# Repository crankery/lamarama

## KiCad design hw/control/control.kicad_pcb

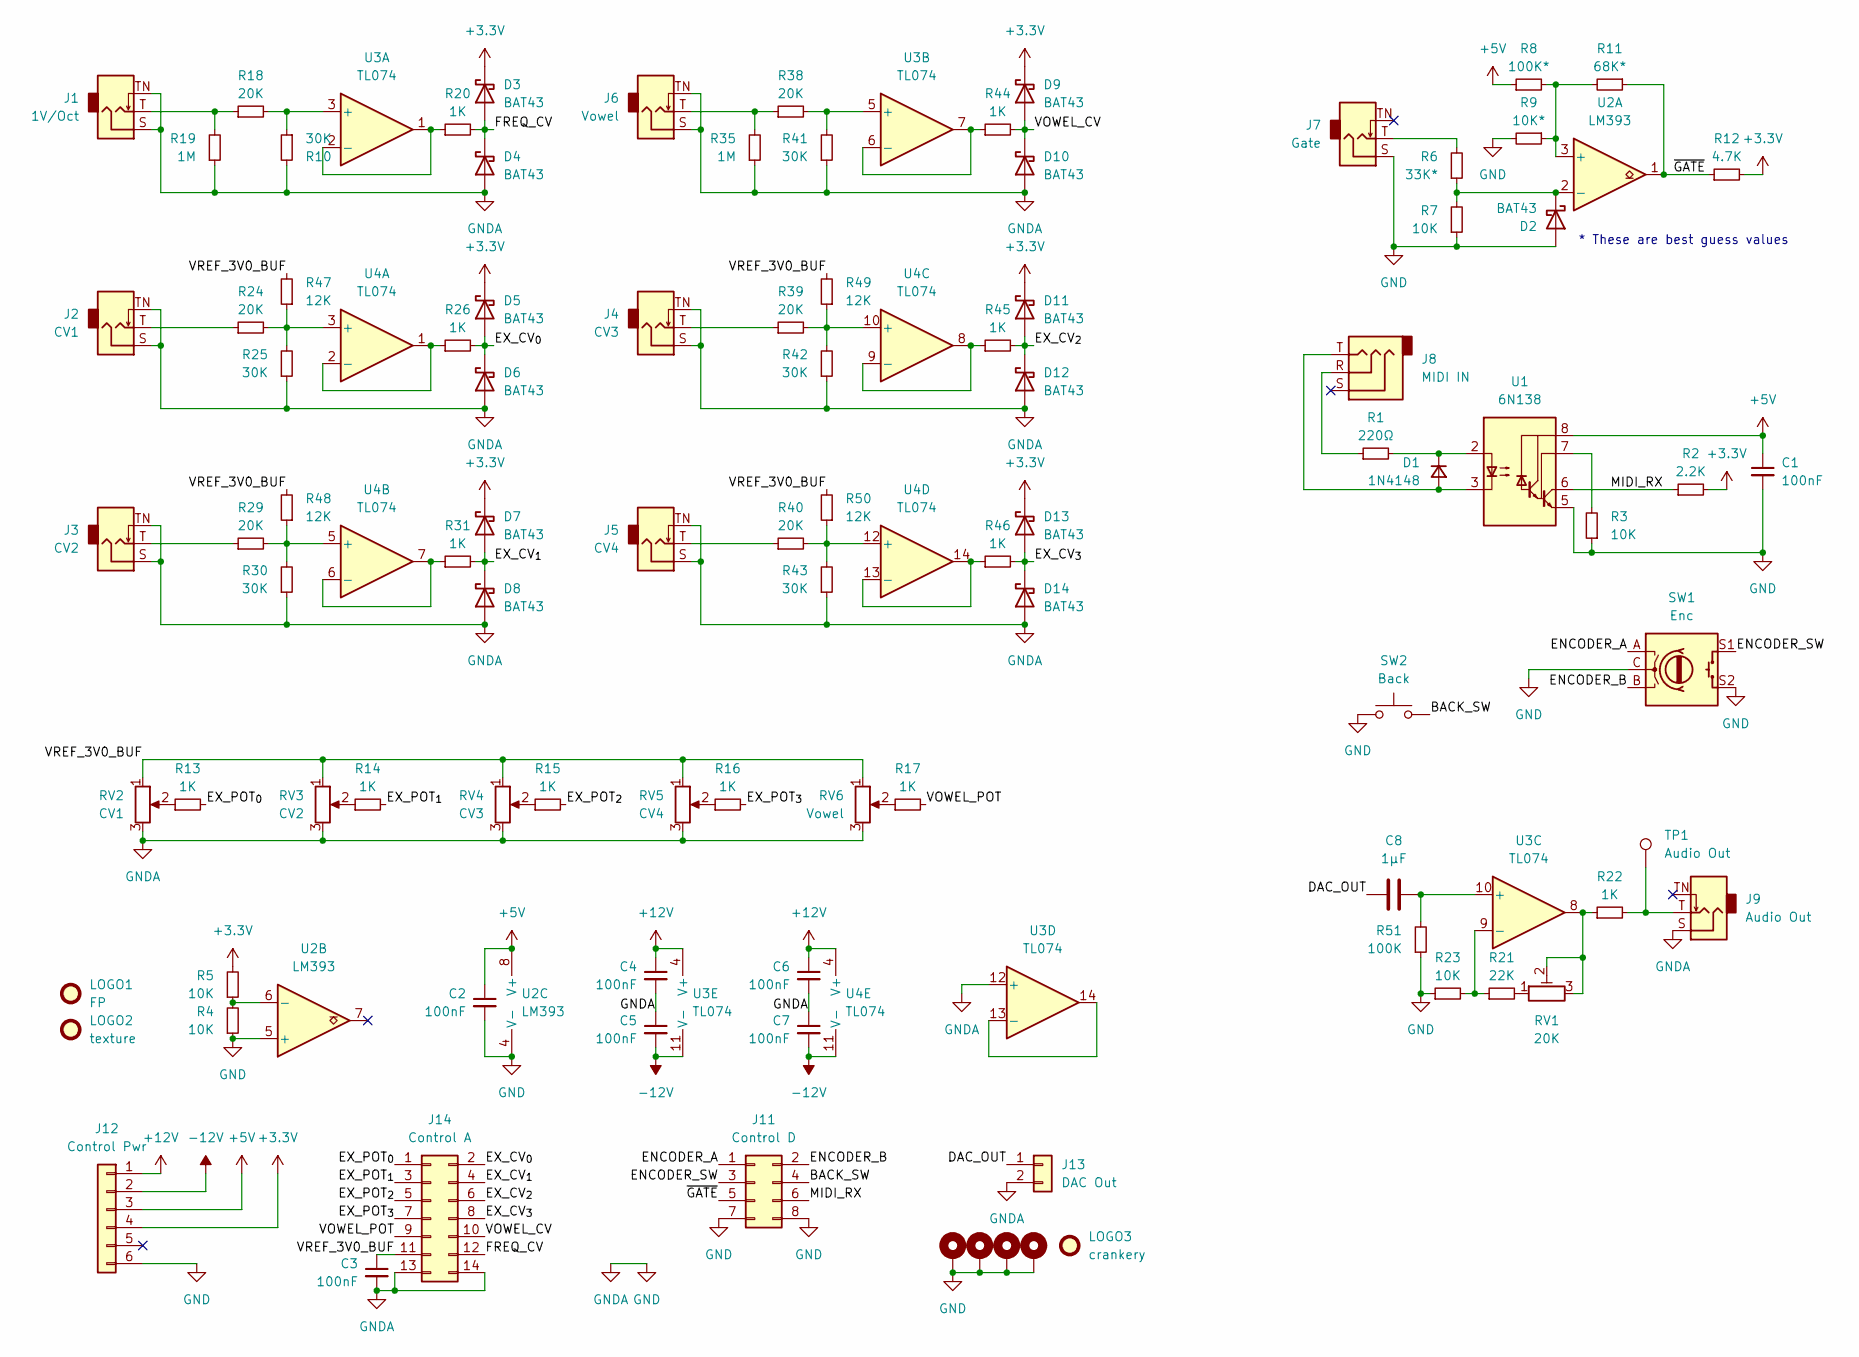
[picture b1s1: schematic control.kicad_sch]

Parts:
C1, C2, C3, C4, C5, C6, C7: 100nF; C_Disc_D3.0mm_W1.6mm_P2.50mm
C8: 1µF; C_Rect_L7.0mm_W2.5mm_P5.00mm
D1: 1N4148; D_DO-35_SOD27_P7.62mm_Horizontal
D2, D3, D4, D5, D6, D7, D8, D9, D10, D11, D12, D13, D14: BAT43; D_DO-35_SOD27_P7.62mm_Horizontal
H1, H2, H3, H4: MountingHole_Pad; MountingHole_3.2mm_M3_DIN965_Pad
J1: 1V/Oct; Jack_PJ398SM
J2: CV1; Jack_PJ398SM
J3: CV2; Jack_PJ398SM
J4: CV3; Jack_PJ398SM
J5: CV4; Jack_PJ398SM
J6: Vowel; Jack_PJ398SM
J7: Gate; Jack_PJ398SM
J8: MIDI IN; Jack_P419_GR
J9: Audio Out; Jack_PJ398SM
J11: Control D; PinHeader_2x04_P2.54mm_Vertical
J12: Control Pwr; PinHeader_1x06_P2.54mm_Vertical
J13: DAC Out; PinHeader_1x02_P2.54mm_Vertical
J14: Control A; PinHeader_2x07_P2.54mm_Vertical
LOGO1: FP; fp
LOGO2: texture; hammeredx
LOGO3: crankery; crankery_small
R1: 220Ω; R_Axial_DIN0204_L3.6mm_D1.6mm_P5.08mm_Horizontal
R2: 2.2K; R_Axial_DIN0204_L3.6mm_D1.6mm_P5.08mm_Horizontal
R3, R4, R5, R7, R23: 10K; R_Axial_DIN0204_L3.6mm_D1.6mm_P5.08mm_Horizontal
R6: 33K*; R_Axial_DIN0204_L3.6mm_D1.6mm_P5.08mm_Horizontal
R8: 100K*; R_Axial_DIN0204_L3.6mm_D1.6mm_P5.08mm_Horizontal
R9: 10K*; R_Axial_DIN0204_L3.6mm_D1.6mm_P5.08mm_Horizontal
R10, R25, R30, R41, R42, R43: 30K; R_Axial_DIN0204_L3.6mm_D1.6mm_P5.08mm_Horizontal
R11: 68K*; R_Axial_DIN0204_L3.6mm_D1.6mm_P5.08mm_Horizontal
R12: 4.7K; R_Axial_DIN0204_L3.6mm_D1.6mm_P5.08mm_Horizontal
R13, R14, R15, R16, R17, R20, R22, R26, R31, R44, R45, R46: 1K; R_Axial_DIN0204_L3.6mm_D1.6mm_P5.08mm_Horizontal
R18, R24, R29, R38, R39, R40: 20K; R_Axial_DIN0204_L3.6mm_D1.6mm_P5.08mm_Horizontal
R19, R35: 1M; R_Axial_DIN0204_L3.6mm_D1.6mm_P5.08mm_Horizontal
R21: 22K; R_Axial_DIN0204_L3.6mm_D1.6mm_P5.08mm_Horizontal
R47, R48, R49, R50: 12K; R_Axial_DIN0204_L3.6mm_D1.6mm_P5.08mm_Horizontal
R51: 100K; R_Axial_DIN0204_L3.6mm_D1.6mm_P5.08mm_Horizontal
RV1: 20K; Potentiometer_Runtron_RM-065_Vertical
RV2: CV1; Potentiometer_Alpha_RD901F-40-00D_Single_Vertical
RV3: CV2; Potentiometer_Alpha_RD901F-40-00D_Single_Vertical
RV4: CV3; Potentiometer_Alpha_RD901F-40-00D_Single_Vertical
RV5: CV4; Potentiometer_Alpha_RD901F-40-00D_Single_Vertical
RV6: Vowel; Potentiometer_Alpha_RD901F-40-00D_Single_Vertical
SW1: Enc; RotaryEncoder_Alps_EC11E-Switch_Vertical_H20mm
SW2: Back; SW_PUSH_6mm_H13mm
TP1: Audio Out; TestPoint_Pad_1.5x1.5mm
U1: 6N138; DIP-8_W7.62mm
U2: LM393; DIP-8_W7.62mm
U3, U4: TL074; DIP-14_W7.62mm

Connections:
+3.3V: D3.1 (K), D5.1 (K), D7.1 (K), D9.1 (K), D11.1 (K), D13.1 (K), J12.4, R2.2, R5.2, R12.2
+5V: C1.1, C2.1, J12.3, R8.1, U1.8 (VCC), U2.8 (V+)
+12V: C4.1, C6.1, J12.1, U3.4 (V+), U4.4 (V+)
-12V: C5.2, C7.2, J12.2, U3.11 (V-), U4.11 (V-)
/BACK_SW: J11.4, SW2.2
/DAC_OUT: C8.1, J13.1
/ENCODER_A: J11.1, SW1.A
/ENCODER_B: J11.2, SW1.B
/ENCODER_SW: J11.3, SW1.S1
/EX_CV_{0}: D5.2 (A), D6.1 (K), J14.2, R26.2
/EX_CV_{1}: D7.2 (A), D8.1 (K), J14.4, R31.2
/EX_CV_{2}: D11.2 (A), D12.1 (K), J14.6, R45.2
/EX_CV_{3}: D13.2 (A), D14.1 (K), J14.8, R46.2
/EX_POT_{0}: J14.1, R13.2
/EX_POT_{1}: J14.3, R14.2
/EX_POT_{2}: J14.5, R15.2
/EX_POT_{3}: J14.7, R16.2
/FREQ_CV: D3.2 (A), D4.1 (K), J14.12, R20.2
/MIDI_RX: J11.6, R2.1, U1.6 (VO2)
/VOWEL_CV: D9.2 (A), D10.1 (K), J14.10, R44.2
/VOWEL_POT: J14.9, R17.2
/VREF_3V0_BUF: C3.1, J14.11, R47.2, R48.2, R49.2, R50.2, RV2.1, RV3.1, RV4.1, RV5.1, RV6.1
/~GATE: J11.5, R11.1, R12.1, U2.1
GND: C1.2, C2.2, C3.2, C4.2, C5.1, C6.2, C7.1, D2.2 (A), D4.2 (A), D6.2 (A), D8.2 (A), D10.2 (A), D12.2 (A), D14.2 (A), H1.1 (1_1), H2.1 (1_1), H3.1 (1_1), H4.1 (1_1), J1.S, J1.TN, J2.S, J2.TN, J3.S, J3.TN, J4.S, J4.TN, J5.S, J5.TN, J6.S, J6.TN, J7.S, J9.S, J11.7, J11.8, J12.6, J13.2, J14.13, J14.14, R3.1, R4.1, R7.1, R9.2, R10.2, R19.1, R23.1, R25.1, R30.1, R35.1, R41.1, R42.1, R43.1, R51.1, RV2.3, RV3.3, RV4.3, RV5.3, RV6.3, SW1.C, SW1.S2, SW2.1, U1.5 (GND), U2.4 (V-), U2.5 (+), U3.12 (+)
unnamed: D1.2 (A), J8.T, U1.3 (C2)
unnamed: D1.1 (K), R1.2, U1.2 (C1)
unnamed: D2.1 (K), R6.1, R7.2, U2.2 (-)
unnamed: J1.T, R18.1, R19.2
unnamed: J2.T, R24.1
unnamed: J3.T, R29.1
unnamed: J4.T, R39.1
unnamed: J5.T, R40.1
unnamed: J6.T, R35.2, R38.1
unnamed: J7.T, R6.2
unnamed: J8.R, R1.1
unnamed: J9.T, R22.2, TP1.1 (1_1)
unnamed: R13.1, RV2.2
unnamed: R14.1, RV3.2
unnamed: R15.1, RV4.2
unnamed: R16.1, RV5.2
unnamed: R17.1, RV6.2
unnamed: R21.2, RV1.1
unnamed: R22.1, RV1.2, RV1.3, U3.8
unnamed: R3.2, U1.7 (VO1)
unnamed: R8.2, R9.1, R11.2, U2.3 (+)
unnamed: R4.2, R5.1, U2.6 (-)
unnamed: R10.1, R18.2, U3.3 (+)
unnamed: R20.1, U3.1, U3.2 (-)
unnamed: R38.2, R41.2, U3.5 (+)
unnamed: R44.1, U3.6 (-), U3.7
unnamed: C8.2, R51.2, U3.10 (+)
unnamed: R21.1, R23.2, U3.9 (-)
unnamed: U3.13 (-), U3.14
unnamed: R24.2, R25.2, R47.1, U4.3 (+)
unnamed: R26.1, U4.1, U4.2 (-)
unnamed: R29.2, R30.2, R48.1, U4.5 (+)
unnamed: R31.1, U4.6 (-), U4.7
unnamed: R39.2, R42.2, R49.1, U4.10 (+)
unnamed: R45.1, U4.8, U4.9 (-)
unnamed: R40.2, R43.2, R50.1, U4.12 (+)
unnamed: R46.1, U4.13 (-), U4.14

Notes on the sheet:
* These are best guess values

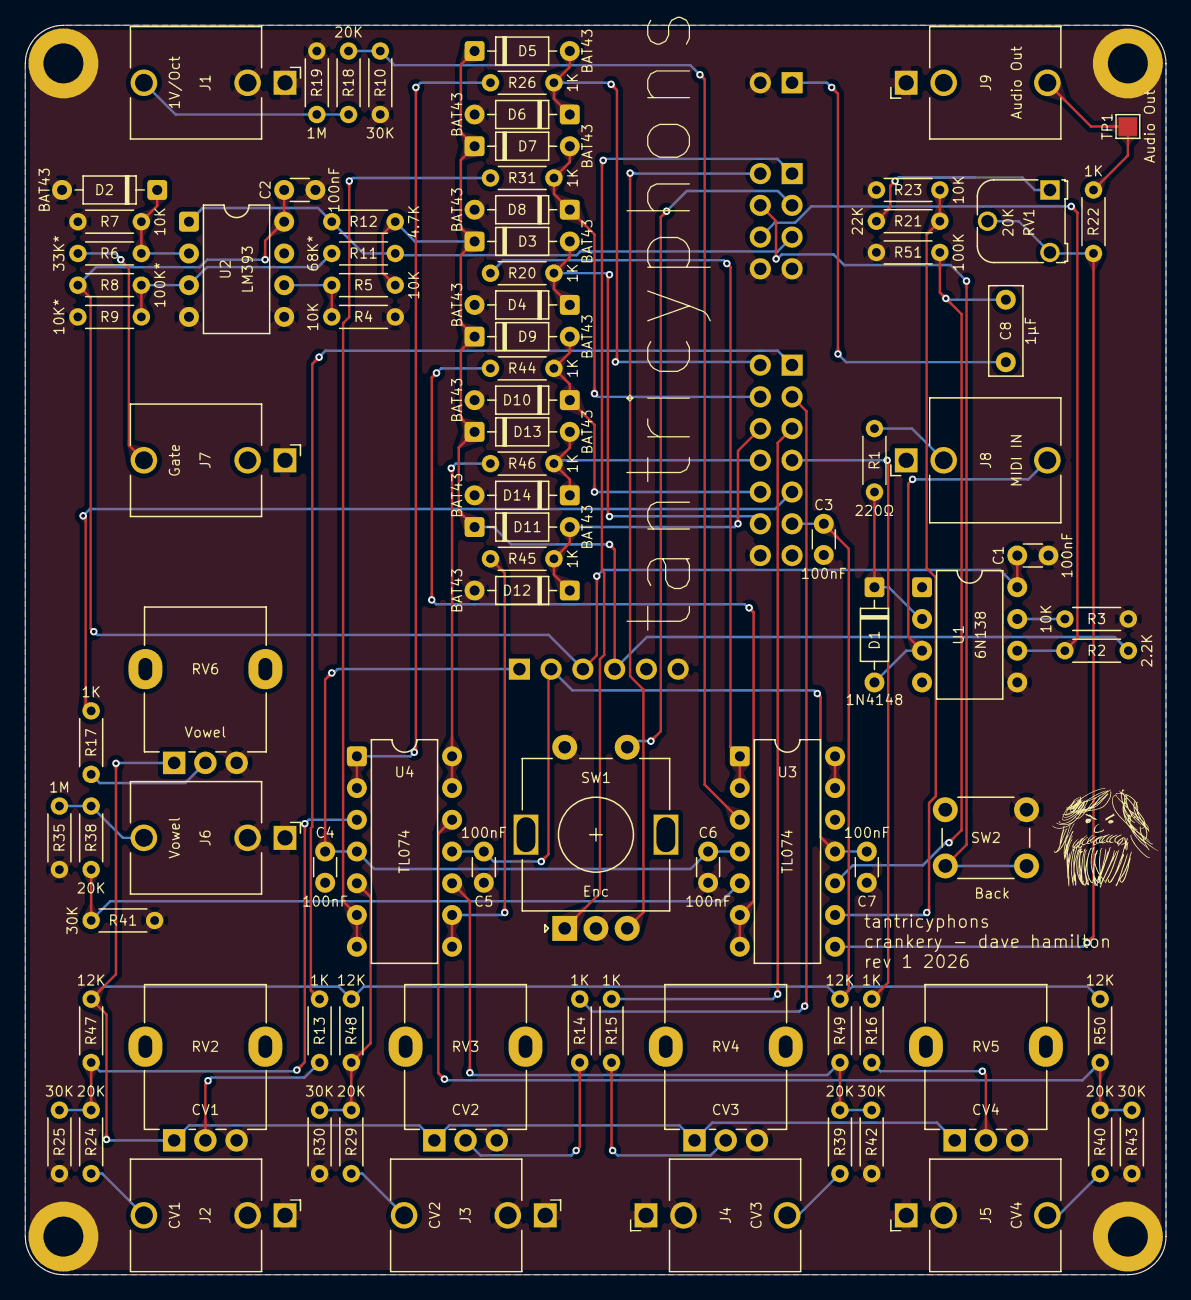
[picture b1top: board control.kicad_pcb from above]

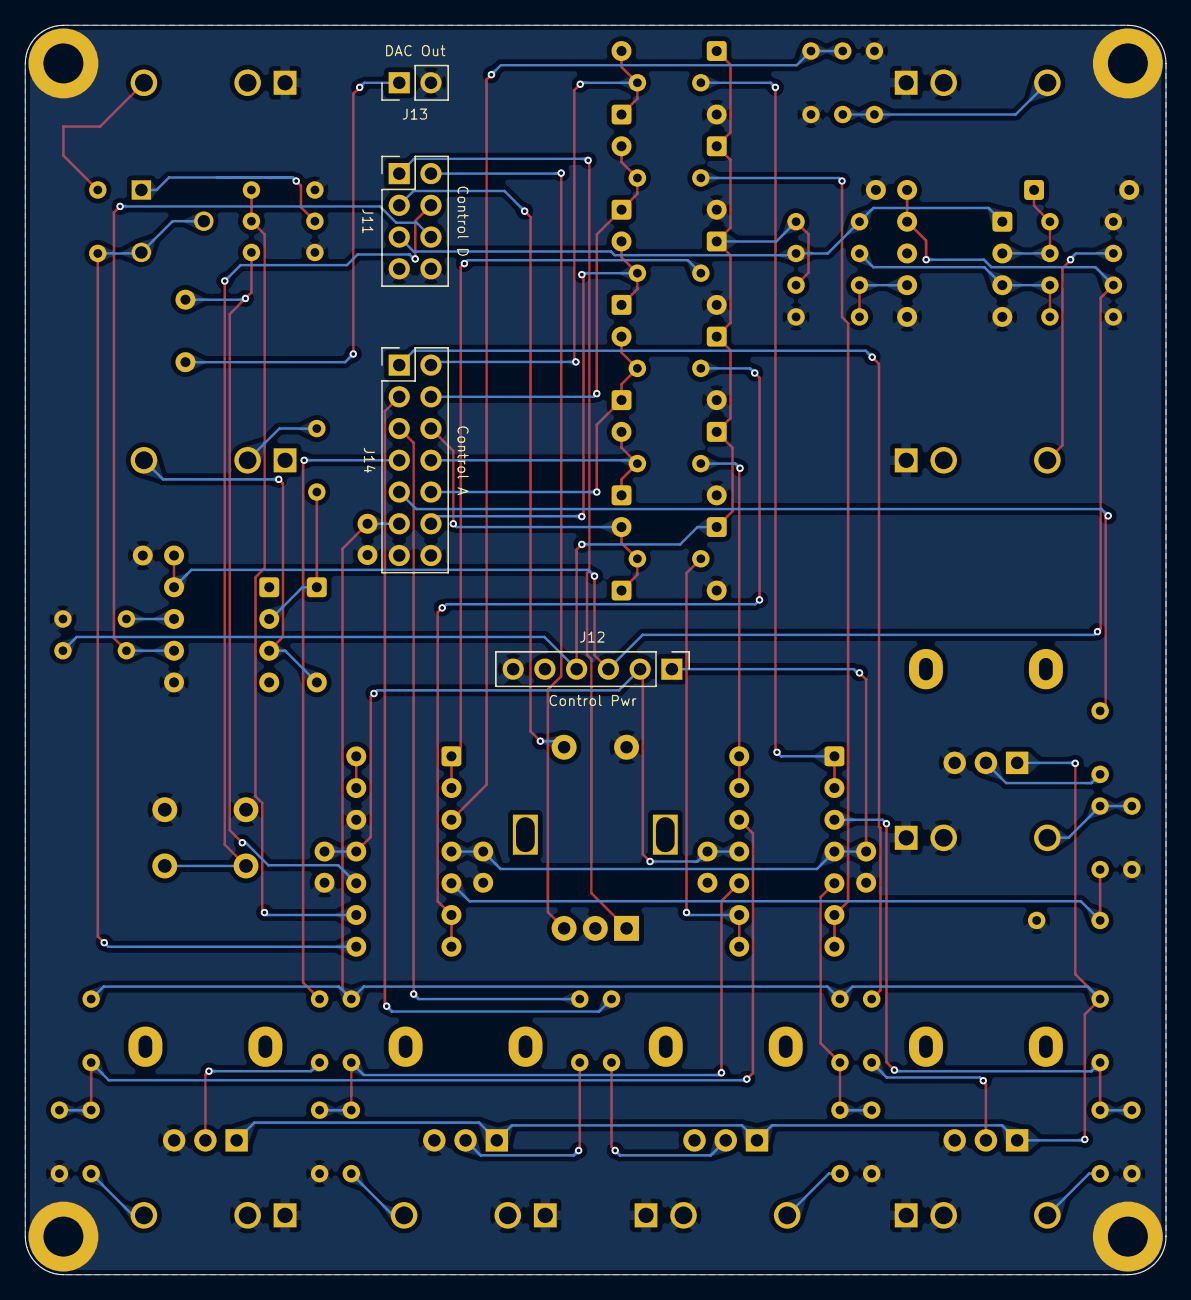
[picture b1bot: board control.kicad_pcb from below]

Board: 2 copper layers, 91.3 x 100.0 mm, 98 parts (4 on the bottom side), 61 nets.

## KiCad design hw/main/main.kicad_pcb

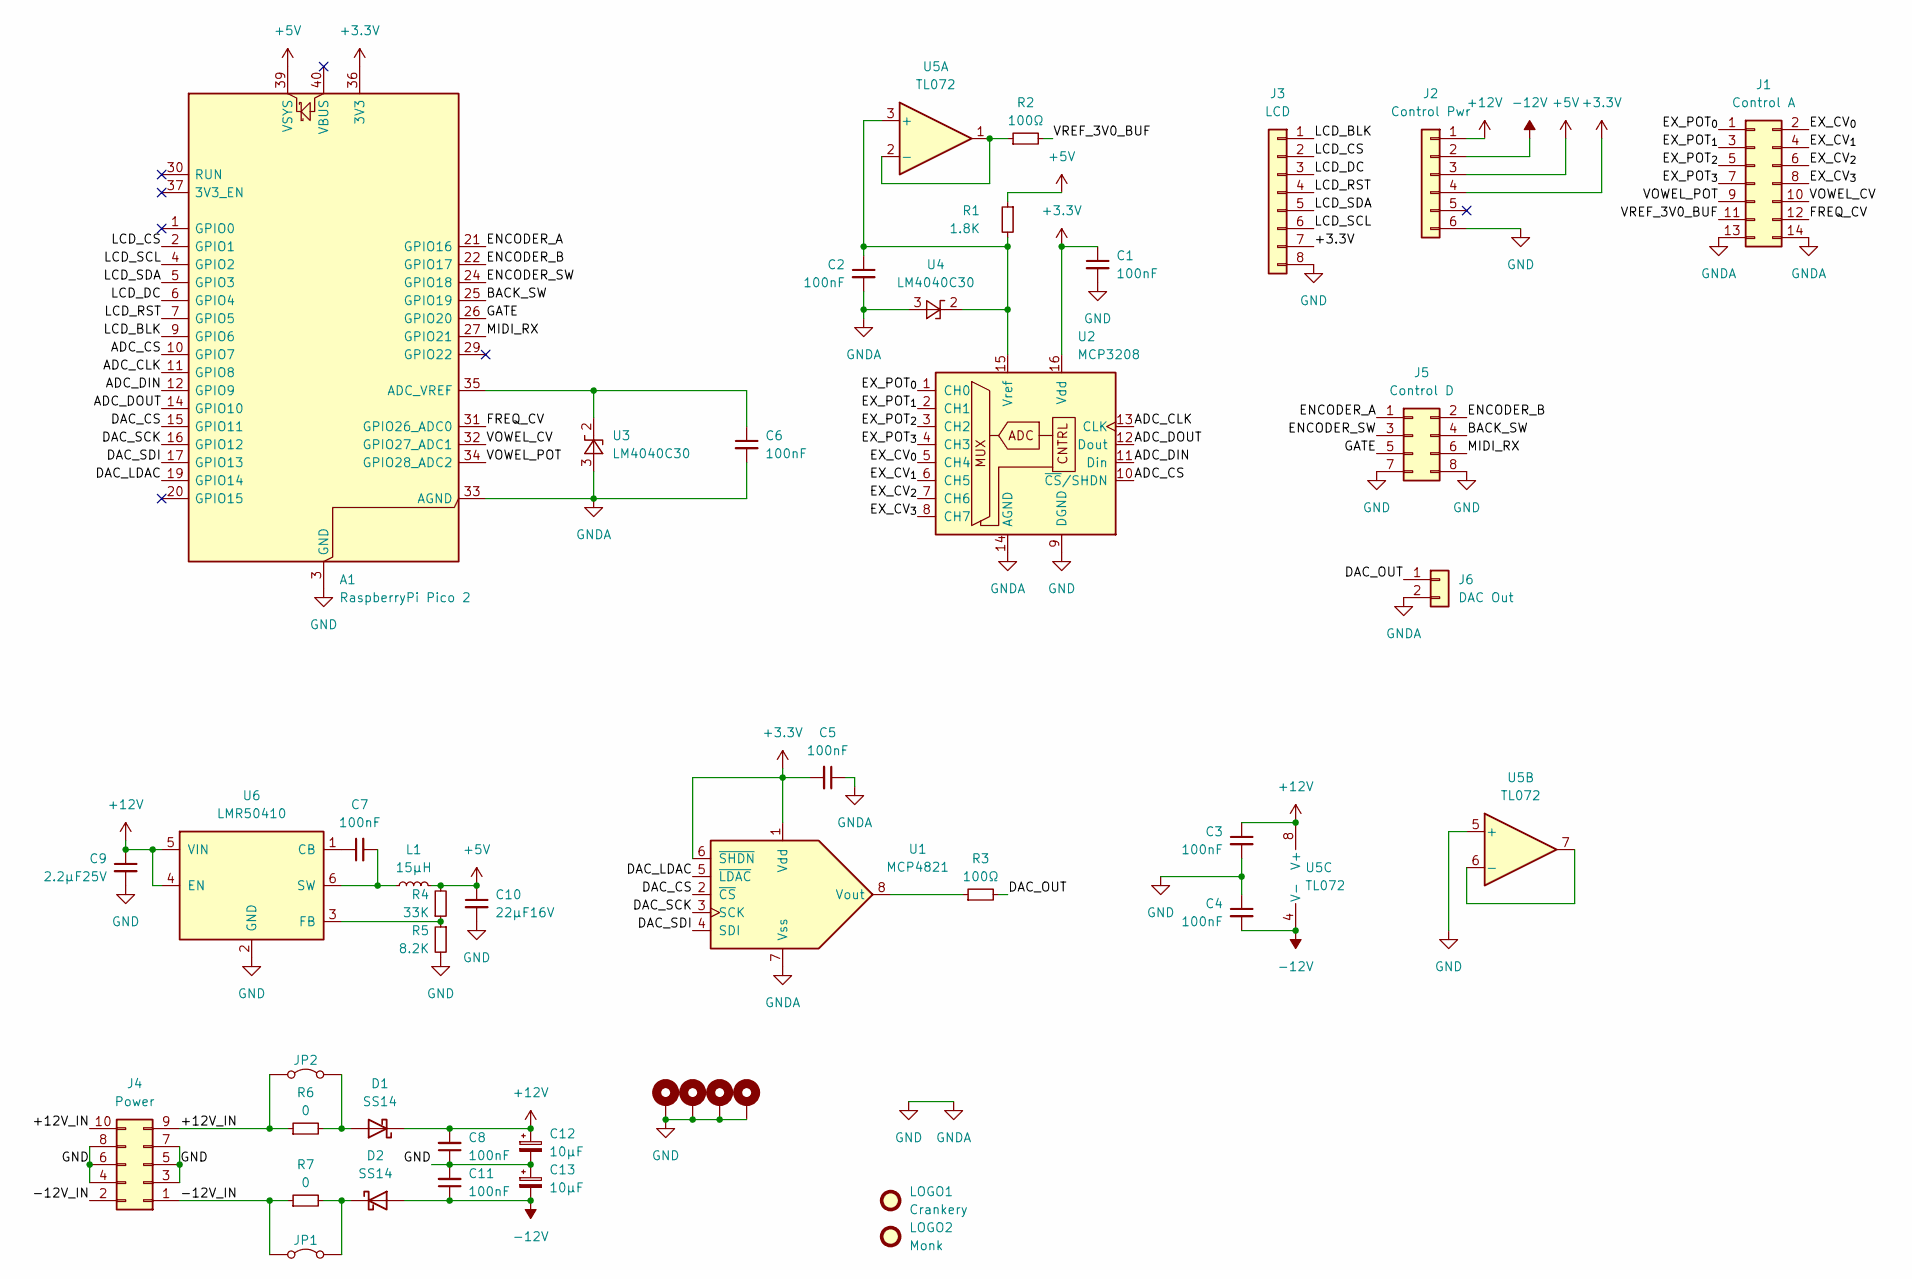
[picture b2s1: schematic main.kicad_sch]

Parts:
A1: RaspberryPi Pico 2; RaspberryPi_Pico_SMD
C1, C2, C3, C4, C5, C6, C8, C11: 100nF; C_Disc_D3.0mm_W1.6mm_P2.50mm
C7: 100nF; C_0805_2012Metric_Pad1.18x1.45mm_HandSolder
C9: 2.2µF25V; C_0805_2012Metric_Pad1.18x1.45mm_HandSolder
C10: 22µF16V; C_1210_3225Metric_Pad1.33x2.70mm_HandSolder
C12, C13: 10µF; CP_Radial_D6.3mm_P2.50mm
D1, D2: SS14; D_SMA
H1, H2, H3, H4: MountingHole_Pad; MountingHole_3.2mm_M3_DIN965_Pad
J1: Control A; PinSocket_2x07_P2.54mm_Vertical
J2: Control Pwr; PinSocket_1x06_P2.54mm_Vertical
J3: LCD; JST_PH_S8B-PH-K_1x08_P2.00mm_Horizontal
J4: Power; IDC-Header_2x05_P2.54mm_Horizontal
J5: Control D; PinSocket_2x04_P2.54mm_Vertical
J6: DAC Out; PinSocket_1x02_P2.54mm_Vertical
JP1, JP2: Jumper_2_Bridged; SolderJumper-2_P1.3mm_Bridged_RoundedPad1.0x1.5mm
L1: 15µH; L_TDK_VLS6045EX_VLS6045AF
LOGO1: Crankery; crankery_small
LOGO2: Monk; monk
R1: 1.8K; R_Axial_DIN0204_L3.6mm_D1.6mm_P5.08mm_Horizontal
R2, R3: 100Ω; R_Axial_DIN0204_L3.6mm_D1.6mm_P5.08mm_Horizontal
R4: 33K; R_0805_2012Metric_Pad1.20x1.40mm_HandSolder
R5: 8.2K; R_0805_2012Metric_Pad1.20x1.40mm_HandSolder
R6, R7: 0; R_Axial_DIN0204_L3.6mm_D1.6mm_P5.08mm_Horizontal
U1: MCP4821; DIP-8_W7.62mm
U2: MCP3208; DIP-16_W7.62mm
U3, U4: LM4040C30; TO-92_Inline
U5: TL072; DIP-8_W7.62mm
U6: LMR50410; SOT-23-6

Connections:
+3.3V: A1.36 (3V3), C1.1, C5.2, J2.4, J3.7, U1.1 (Vdd), U1.6 (~SHDN), U2.16 (Vdd)
+5V: A1.39 (VSYS), C10.1, J2.3, L1.2, R1.1, R4.2
+12V: C3.1, C8.2, C9.1, C12.1, D1.1 (K), J2.1, U5.8 (V+), U6.4 (EN), U6.5 (VIN)
-12V: C4.2, C11.1, C13.2, D2.2 (A), J2.2, U5.4 (V-)
/+12V_IN: J4.9, J4.10, JP2.1 (A), R6.1
/-12V_IN: J4.1, J4.2, JP1.1 (A), R7.1
/ADC_CLK: A1.11 (GPIO8), U2.13 (CLK)
/ADC_CS: A1.10 (GPIO7), U2.10 (~CS/SHDN)
/ADC_DIN: A1.12 (GPIO9), U2.11 (Din)
/ADC_DOUT: A1.14 (GPIO10), U2.12 (Dout)
/BACK_SW: A1.25 (GPIO19), J5.4
/DAC_CS: A1.15 (GPIO11), U1.2 (~CS)
/DAC_LDAC: A1.19 (GPIO14), U1.5 (~LDAC)
/DAC_OUT: J6.1, R3.2
/DAC_SCK: A1.16 (GPIO12), U1.3 (SCK)
/DAC_SDI: A1.17 (GPIO13), U1.4 (SDI)
/ENCODER_A: A1.21 (GPIO16), J5.1
/ENCODER_B: A1.22 (GPIO17), J5.2
/ENCODER_SW: A1.24 (GPIO18), J5.3
/EX_CV_{0}: J1.2, U2.5 (CH4)
/EX_CV_{1}: J1.4, U2.6 (CH5)
/EX_CV_{2}: J1.6, U2.7 (CH6)
/EX_CV_{3}: J1.8, U2.8 (CH7)
/EX_POT_{0}: J1.1, U2.1 (CH0)
/EX_POT_{1}: J1.3, U2.2 (CH1)
/EX_POT_{2}: J1.5, U2.3 (CH2)
/EX_POT_{3}: J1.7, U2.4 (CH3)
/FREQ_CV: A1.31 (GPIO26_ADC0), J1.12
/GATE: A1.26 (GPIO20), J5.5
/LCD_BLK: A1.9 (GPIO6), J3.1
/LCD_CS: A1.2 (GPIO1), J3.2
/LCD_DC: A1.6 (GPIO4), J3.3
/LCD_RST: A1.7 (GPIO5), J3.4
/LCD_SCL: A1.4 (GPIO2), J3.6
/LCD_SDA: A1.5 (GPIO3), J3.5
/MIDI_RX: A1.27 (GPIO21), J5.6
/VOWEL_CV: A1.32 (GPIO27_ADC1), J1.10
/VOWEL_POT: A1.34 (GPIO28_ADC2), J1.9
/VREF_3V0_BUF: J1.11, R2.2
GND: A1.3 (GND), A1.8 (GND), A1.13 (GND), A1.18 (GND), A1.23 (GND), A1.28 (GND), A1.33 (AGND), A1.38 (GND), C1.2, C2.2, C3.2, C4.1, C5.1, C6.2, C8.1, C9.2, C10.2, C11.2, C12.2, C13.1, H1.1 (1_1), H2.1 (1_1), H3.1 (1_1), H4.1 (1_1), J1.13, J1.14, J2.6, J3.8, J4.3, J4.4, J4.5, J4.6, J4.7, J4.8, J5.7, J5.8, J6.2, R5.2, U1.7 (Vss), U2.9 (DGND), U2.14 (AGND), U3.3 (A), U4.3 (A), U5.5 (+), U6.2 (GND)
unnamed: A1.35 (ADC_VREF), C6.1, U3.2 (K)
unnamed: D1.2 (A), JP2.2 (B), R6.2
unnamed: D2.1 (K), JP1.2 (B), R7.2
unnamed: R3.1, U1.8 (Vout)
unnamed: C2.1, R1.2, U2.15 (Vref), U4.2 (K), U5.3 (+)
unnamed: R2.1, U5.1, U5.2 (-)
unnamed: U5.6 (-), U5.7
unnamed: C7.1, U6.1 (CB)
unnamed: R4.1, R5.1, U6.3 (FB)
unnamed: C7.2, L1.1, U6.6 (SW)

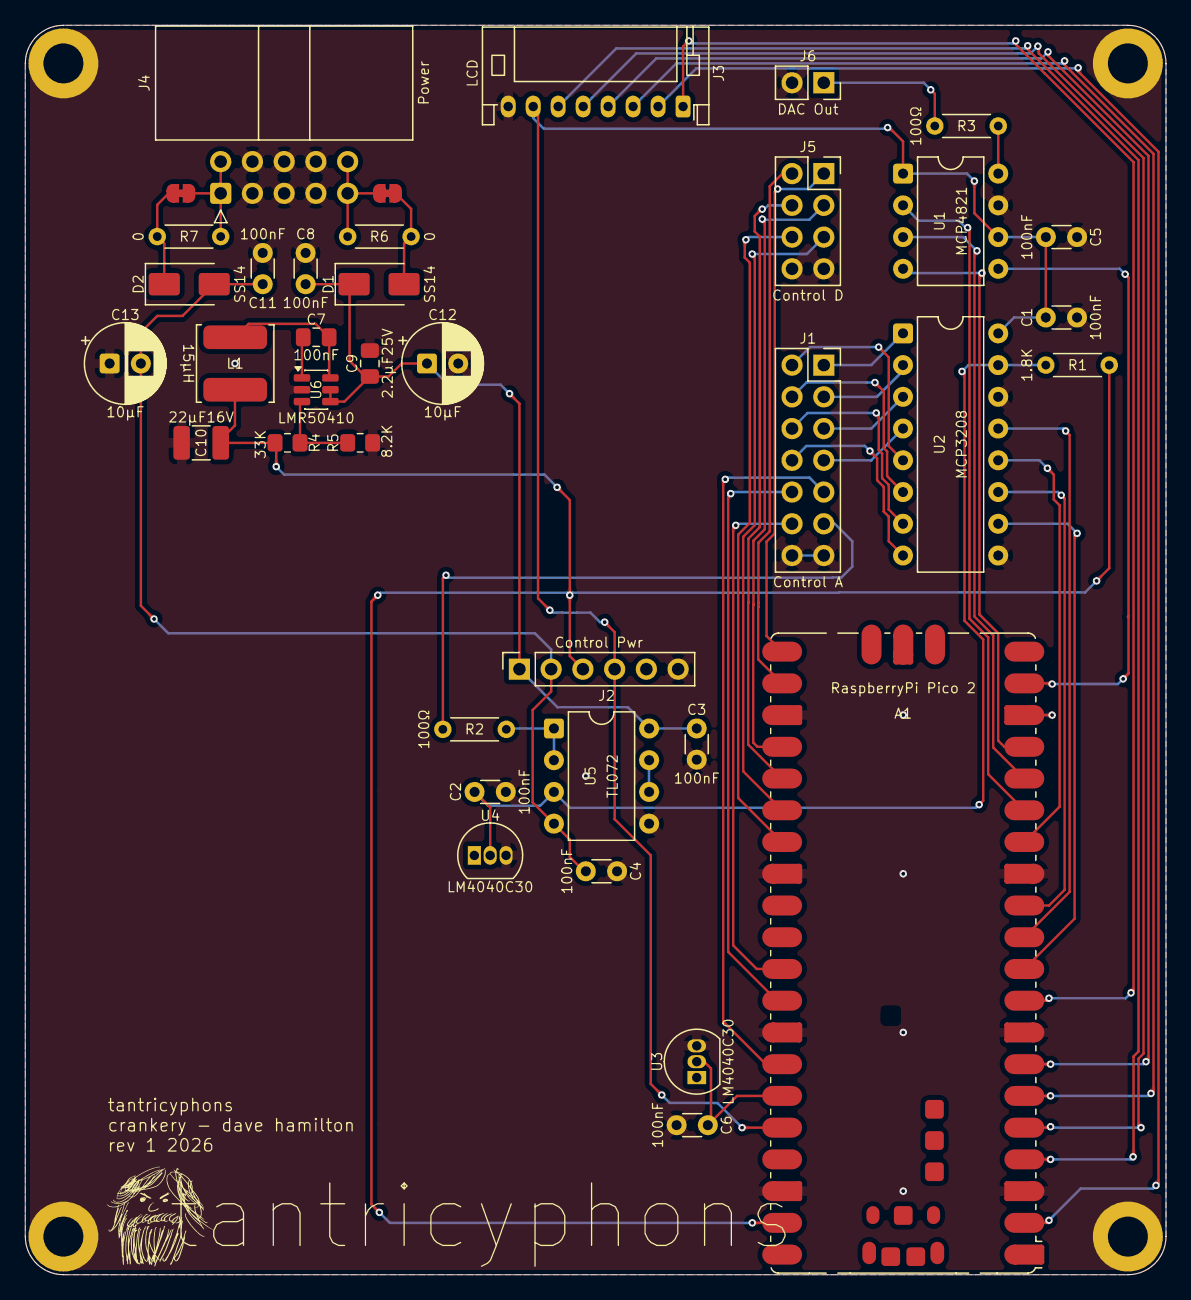
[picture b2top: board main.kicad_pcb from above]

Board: 2 copper layers, 91.3 x 100.0 mm, 44 parts (1 on the bottom side), 50 nets.

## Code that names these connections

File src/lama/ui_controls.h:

#ifndef LAMA_UI_CONTROLS_H
#define LAMA_UI_CONTROLS_H

#define ENCODER_A 16
#define ENCODER_B 17
#define ENCODER_SW 18
#define BACK_SW 19

/* PIO2 counts GP16/17 edges. Active-low OK/Back use pull-ups and debounce.
 * Four quadrature edges per detent; see encoder_steps.h. */
void ui_controls_init(void);
void ui_controls_poll(void);

#endif

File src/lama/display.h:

#ifndef LAMA_DISPLAY_H
#define LAMA_DISPLAY_H
#include <stdbool.h>

#define LCD_CS 1
#define LCD_SCK 2
#define LCD_MOSI 3
#define LCD_DC 4
#define LCD_RST 5
#define LCD_BLK 6
/* Conservative bring-up setting; actual SPI rate depends on clk_peri. */
#define DISPLAY_SPI_HZ 12500000

/* Core 0 only. Init starts an asynchronous panel reset; poll every UI loop.
 * ST7789, portrait 240x320, RGB565, zero panel offsets. */
void display_init(void);
void display_poll(void);
bool display_ready_for_flash(void);
#endif

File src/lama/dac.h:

#ifndef LAMA_DAC_H
#define LAMA_DAC_H

#include <stdint.h>

#define DAC_CS 11
#define DAC_SCK 12
#define DAC_SDI 13
#define DAC_LDAC 14

typedef struct
{
    uint32_t starts[2], completions[2];
    uint32_t late_buffers; /* Next RAM buffer not ready at DMA completion */
    uint32_t underruns;    /* Observed PIO TXSTALL episodes; sticky/coalesced */
    uint32_t block_budget_us;
    int active_buffer; /* -1 when no DMA transfer is active */
} DacDebugStats;

/* Core 1 only; audio core republishes these for core 0. */
DacDebugStats dac_get_debug_stats(void);

/* All calls run on core 1. Acquire blocks until a buffer is free; submit
 * transfers ownership to DMA. Never write a buffer after submitting it. */
void dac_init(void);
uint16_t *get_free_dac_buffer(void);
void submit_dac_buffer(uint16_t *buffer);

#endif

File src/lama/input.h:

#ifndef LAMA_INPUT_H
#define LAMA_INPUT_H

#include <stdbool.h>
#include <stdint.h>

#define INPUT_PICO_CHANNELS 3
#define INPUT_EXTERNAL_CHANNELS 8
#define INPUT_SCAN_INTERVAL_US 1000
#define ADC_CS 7
#define ADC_CLK 8
#define ADC_DIN 9
#define ADC_DOUT 10

/* Channel indices are physical ADC channels, with no voice assignments.
 * Raw range is 0..4095; each converter has its own voltage reference.
 * A snapshot is published only after both converters finish a full scan. */
typedef struct
{
    uint16_t pico[INPUT_PICO_CHANNELS];         /* ADC0..2 = GP26..28 */
    uint16_t external[INPUT_EXTERNAL_CHANNELS]; /* MCP3208 CH0..7 */
    float pico_normalized[INPUT_PICO_CHANNELS]; /* calibrated 0..1 */
    float external_normalized[INPUT_EXTERNAL_CHANNELS];
    uint32_t sequence;
    uint64_t timestamp_us;
} InputSnapshot;

typedef enum
{
    INPUT_ADC_PICO,   /* channels 0..2, GP26..28 */
    INPUT_ADC_MCP3208 /* channels 0..7 */
} InputAdc;

/* Called once per channel after each valid full scan, even if unchanged.
 * Runs inside poll_controls() on core 0, outside the snapshot lock.
 * Keep it short and nonblocking. Values are raw 0..4095. */
typedef void (*InputUpdateHandler)(InputAdc adc, unsigned channel, uint16_t value);

/* Set on core 0; NULL disables notifications. Registration persists across
 * input_init(). No notifications are generated for discarded scans. */
void input_set_update_handler(InputUpdateHandler handler);

/* Initialize and poll on core 0. Poll is nonblocking; call every UI loop.
 * Snapshot reads are safe from either core, outside interrupt handlers. */
void input_init(void);
void poll_controls(void);
bool input_get_snapshot(InputSnapshot *snapshot);

#endif
